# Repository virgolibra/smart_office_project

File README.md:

# smart_office_project

This is the repo for MSc CE dissertation.

### Introduce

The project introduces a method to build a seat occupancy system with a smart IoT office system. It contains three subsystems, which are smart chair system, smart desk occupancy system and smart desktop clock system, to provide desk occupancy monitoring, chair occupancy monitoring, desk check-in and out, and office indoor environmental parameter measurement. A Flutter App is designed for user interaction and data visualisation. 3D print PLA enclosure are used for sensor boxes. The system can be deployed in the office or study space.

------

### Hardware Requirements

+ Seat pressure sensors and Zigbee binary sensors.
+ Infrared motion sensor with ESP8266 NodeMCU module.
+ Integrated desktop clock with Arduino Nano 33 IoT.

##### Components List

+ Hub and Gateway

  + Raspberry Pi
  + ConBee II ZigBee Gateway

+ Chair sensor

  + Aqara water leak sensor

  + Seat pressure sensor

  + CR2032 Lithium Battery

+ Smart Desktop Clock

  + Arduino Nano 33 IoT
  + NeoPixel Stick
  + RC522 RFID module
  + BMP180 Sensor
  + TM1637 4-digits Display

+ Smart Desk Occupancy System

  + Lithium polymer ion battery
  + ESP8266 NodeMCU
  + HC-SR312 PIR motion sensor

+ Circuit board components

  + Stripboards
  + Solid wires
  + Connectors

+ Enclosures

  + 3D printed boxes and connectors
  + Cushion 

----------

### Software requirements

#### Home Assistant Installation

**Prerequisites:** 

1. Raspberry Pi 4
2. Power supply
3. SD card reader
4. Micro SD card

**Boot media:**

1. Attach SD card to computer as the boot media.
2. Download flasher software. ([Balena Etcher](https://www.balena.io/etcher/))
3. Flash from URL ```https://github.com/home-assistant/operating-system/releases/download/8.4/haos_rpi4-64-8.4.img.xz``` for Raspberry Pi 4 64-bit.
4. Download image, select SD card and flash.

**Setup Wi-Fi:**

1. Place the flashed SD card to a Windows PC.

2. Open it with file explorer.

3. Create a new folder named "CONFIG".

4. Open the folder and create another folder named "network"

5. Open the "network" folder create a plain text file named "my-network".

6. Edit it as follows. The [online UUID generator](https://www.uuidgenerator.net/version1)

   ```properties
   [connection]
   id=my-network
   uuid=72111c67-4a5d-4d5c-925e-f8ee26efb3c3
   type=802-11-wireless
   
   [802-11-wireless]
   mode=infrastructure
   ssid=MY_SSID
   # Uncomment below if your SSID is not broadcasted
   #hidden=true
   
   [802-11-wireless-security]
   auth-alg=open
   key-mgmt=wpa-psk
   psk=MY_WLAN_SECRET_KEY
   
   [ipv4]
   method=auto
   
   [ipv6]
   addr-gen-mode=stable-privacy
   method=auto
   ```

7. Save the changes, remove the SD card and plug into Raspberry Pi.
8. Boot Raspberry Pi, the specified network should be connected.

**Config Home Assistant**

1. After network connection, Home Assistant can be accessed in the browser of the Desktop system on `homeassistant.local:8123`, or `homeassistant:8123`, or `http://[IPAddress]:8123`in a few minutes.
2. Follow the instructions in [Home Assistant official guideline](https://www.home-assistant.io/getting-started/onboarding/).

#### Flutter Mobile App

**Prerequisites:** 

1. Any Operating System (Linux, Windows, MacOS etc.)
2. Any IDE with Flutter SDK installed (VSCode, Android Studio, XCode, etc.)
3. Basic knowledge and practice of Flutter and Dart.
4. Setup Firebase App based on [Firebase official guideline](https://firebase.google.com/docs/guides).

**Dependencies:**

```yaml
  cupertino_icons: ^1.0.2
  cloud_firestore: ^3.1.14
  firebase_auth: ^3.3.17
  firebase_core: ^1.12.0
  firebase_storage: ^10.2.16
  provider: ^6.0.2
  google_fonts: ^2.3.2
  bottom_bar: ^1.3.0+1
  geolocator: ^8.2.0
  weather: ^2.0.1
  mqtt_client: ^9.6.2
  camera: ^0.9.4+21
```

----

### Data Visualisation

#### Grafana with InfluxDB in Home Assistant

Home Assistant 

Grafana

App

----

### Application Demo YouTube Link

https://youtube.com/shorts/BBJ_iGN9C2Y?feature=share

-----

## Contact Details

If you have any questions, please feel free to contact me: [minghao.zhang.21@ucl.ac.uk](https://github.com/virgolibra/casa0015-mobile-assessment/blob/master/minghao.zhang.21@ucl.ac.uk)

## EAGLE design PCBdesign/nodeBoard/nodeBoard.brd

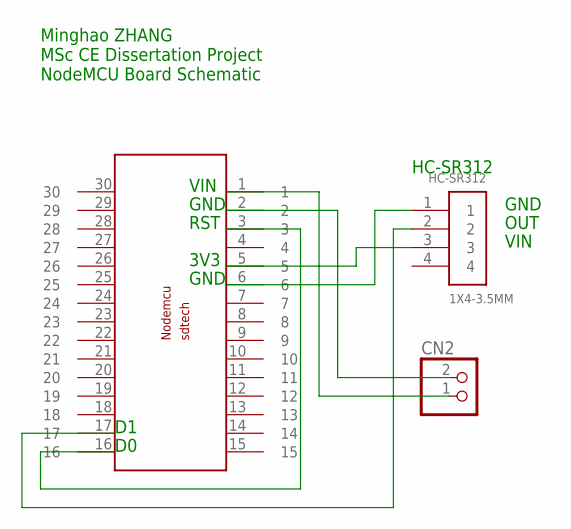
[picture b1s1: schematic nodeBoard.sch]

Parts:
CN2: JST_2PIN-SMT; JST-PH-2-SMT
HC-SR312: 1X4-3.5MM; 1X04-3.5MM
U$1: NODEMCUESP8266

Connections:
unnamed: CN2.1 (2), U$1.1
unnamed: CN2.2 (1), U$1.2
unnamed: HC-SR312.2, U$1.17
unnamed: HC-SR312.3, U$1.5
unnamed: HC-SR312.1, U$1.6
unnamed: U$1.3, U$1.16

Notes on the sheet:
Minghao ZHANG MSc CE Dissertation Project NodeMCU Board Schematic
HC-SR312
OUT
GND
VIN
RST
3V3

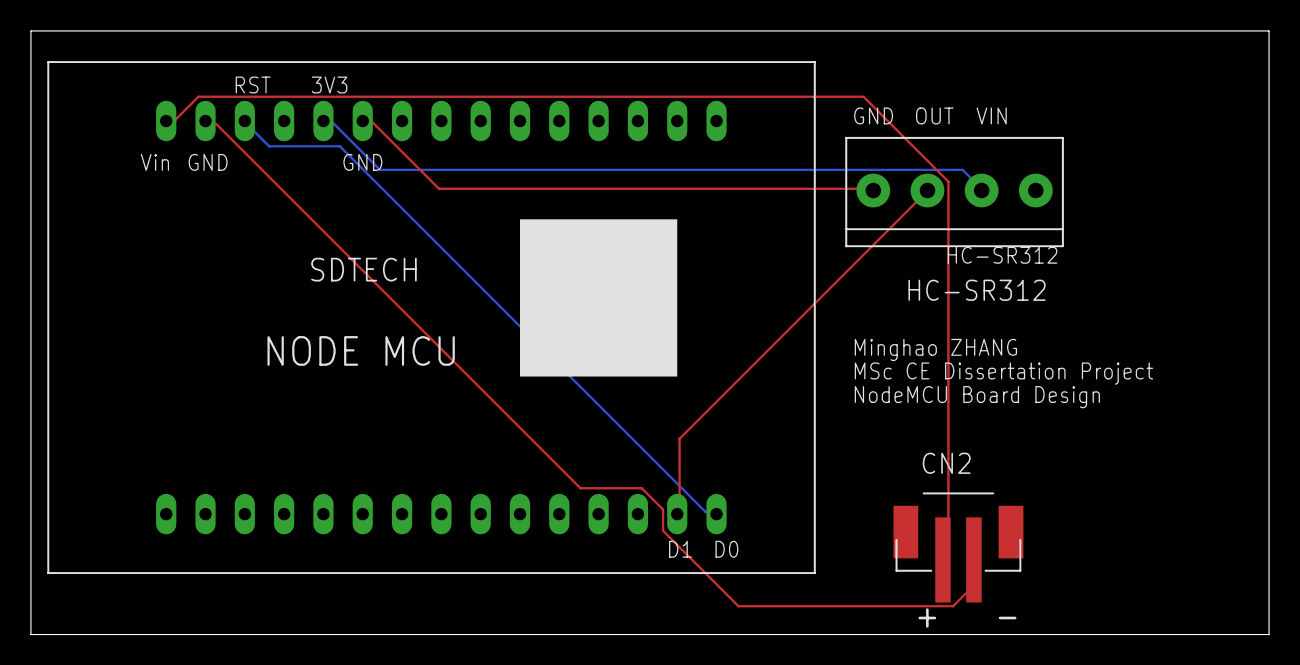
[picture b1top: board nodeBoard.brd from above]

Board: 2 copper layers, 80.0 x 39.0 mm, 3 parts (0 on the bottom side), 6 nets.

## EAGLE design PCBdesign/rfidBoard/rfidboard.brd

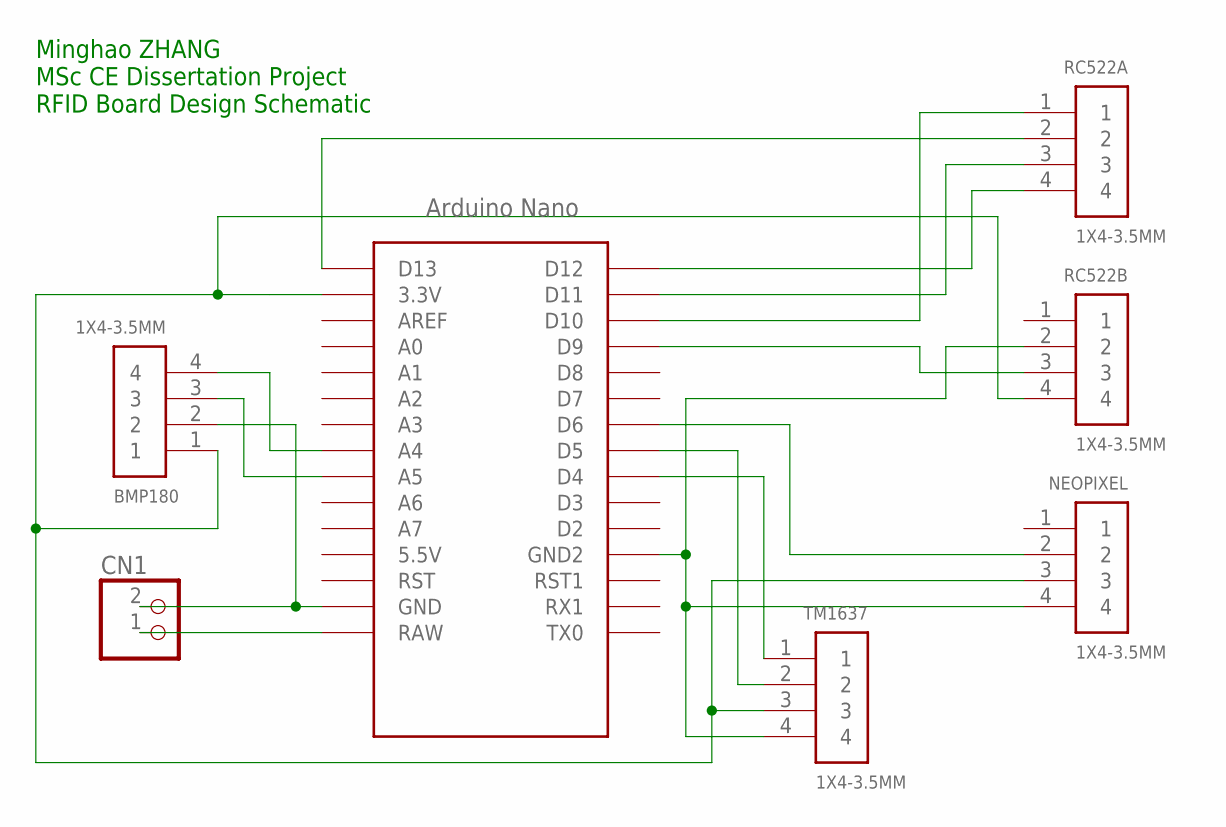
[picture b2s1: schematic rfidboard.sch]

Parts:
BMP180: 1X4-3.5MM; 1X04-3.5MM
CN1: JST_2PIN-SMT; JST-PH-2-SMT
NEOPIXEL: 1X4-3.5MM; 1X04-3.5MM
RC522A, RC522B: 1X4-3.5MM; 1X04-3.5MM
TM1637: 1X4-3.5MM; 1X04-3.5MM
U$1: NANO

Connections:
unnamed: CN1.1 (2), U$1.RAW
unnamed: BMP180.2, CN1.2 (1), U$1.GND
unnamed: TM1637.1, U$1.D4
unnamed: TM1637.2, U$1.D5
unnamed: BMP180.1, NEOPIXEL.3, RC522B.4, TM1637.3, U$1.3.3V
unnamed: NEOPIXEL.4, RC522B.2, TM1637.4, U$1.GND1 (GND2)
unnamed: NEOPIXEL.2, U$1.D6
unnamed: RC522A.1, U$1.D10
unnamed: BMP180.4, U$1.A4
unnamed: BMP180.3, U$1.A5
unnamed: RC522A.2, U$1.D13
unnamed: RC522A.3, U$1.D11
unnamed: RC522A.4, U$1.D12
unnamed: RC522B.3, U$1.D9

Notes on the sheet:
Minghao ZHANG MSc CE Dissertation Project RFID Board Design Schematic

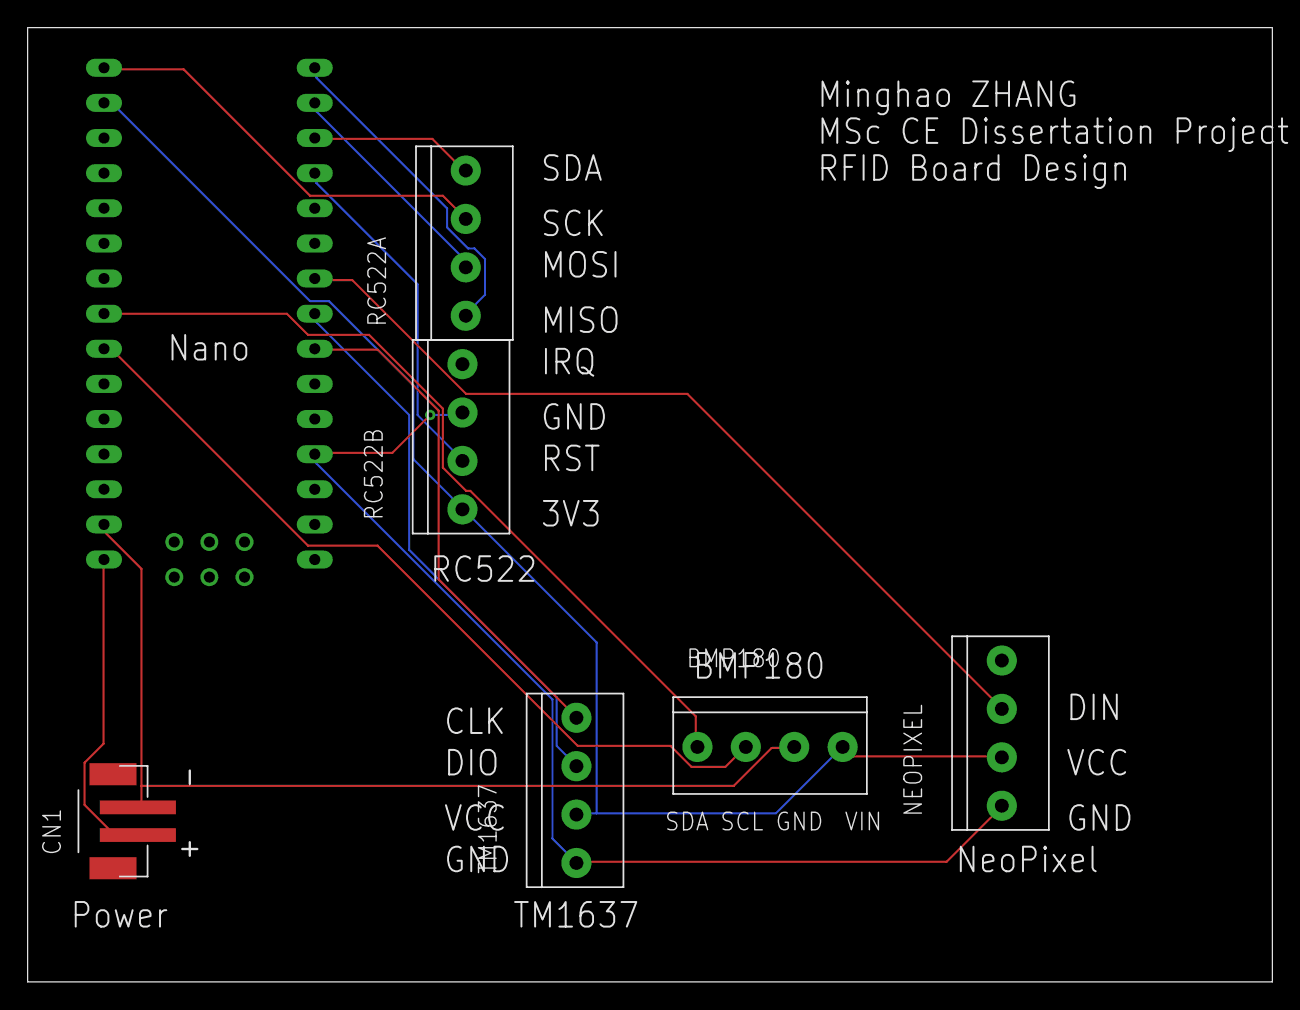
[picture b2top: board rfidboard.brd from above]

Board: 2 copper layers, 90.0 x 69.0 mm, 7 parts (0 on the bottom side), 14 nets.

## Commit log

2022-07-31 create new flutter app
2022-07-31 update build gradle
2022-07-31 create firebase app
2022-07-31 add pages and asset
2022-08-01 update app pages
2022-08-01 test Mqtt function
2022-08-14 update mqtt
2022-08-14 update assets
2022-08-14 update ui
2022-08-15 update weather UI
2022-08-15 update mqtt function
2022-08-15 update chair function
2022-08-16 update desk mqtt
2022-08-16 update checkin
2022-08-16 update firebase
2022-08-16 update firebase function
2022-08-20 update dependency description
2022-08-21 fix text
2022-08-22 update materials
2022-08-22 update 3d models
